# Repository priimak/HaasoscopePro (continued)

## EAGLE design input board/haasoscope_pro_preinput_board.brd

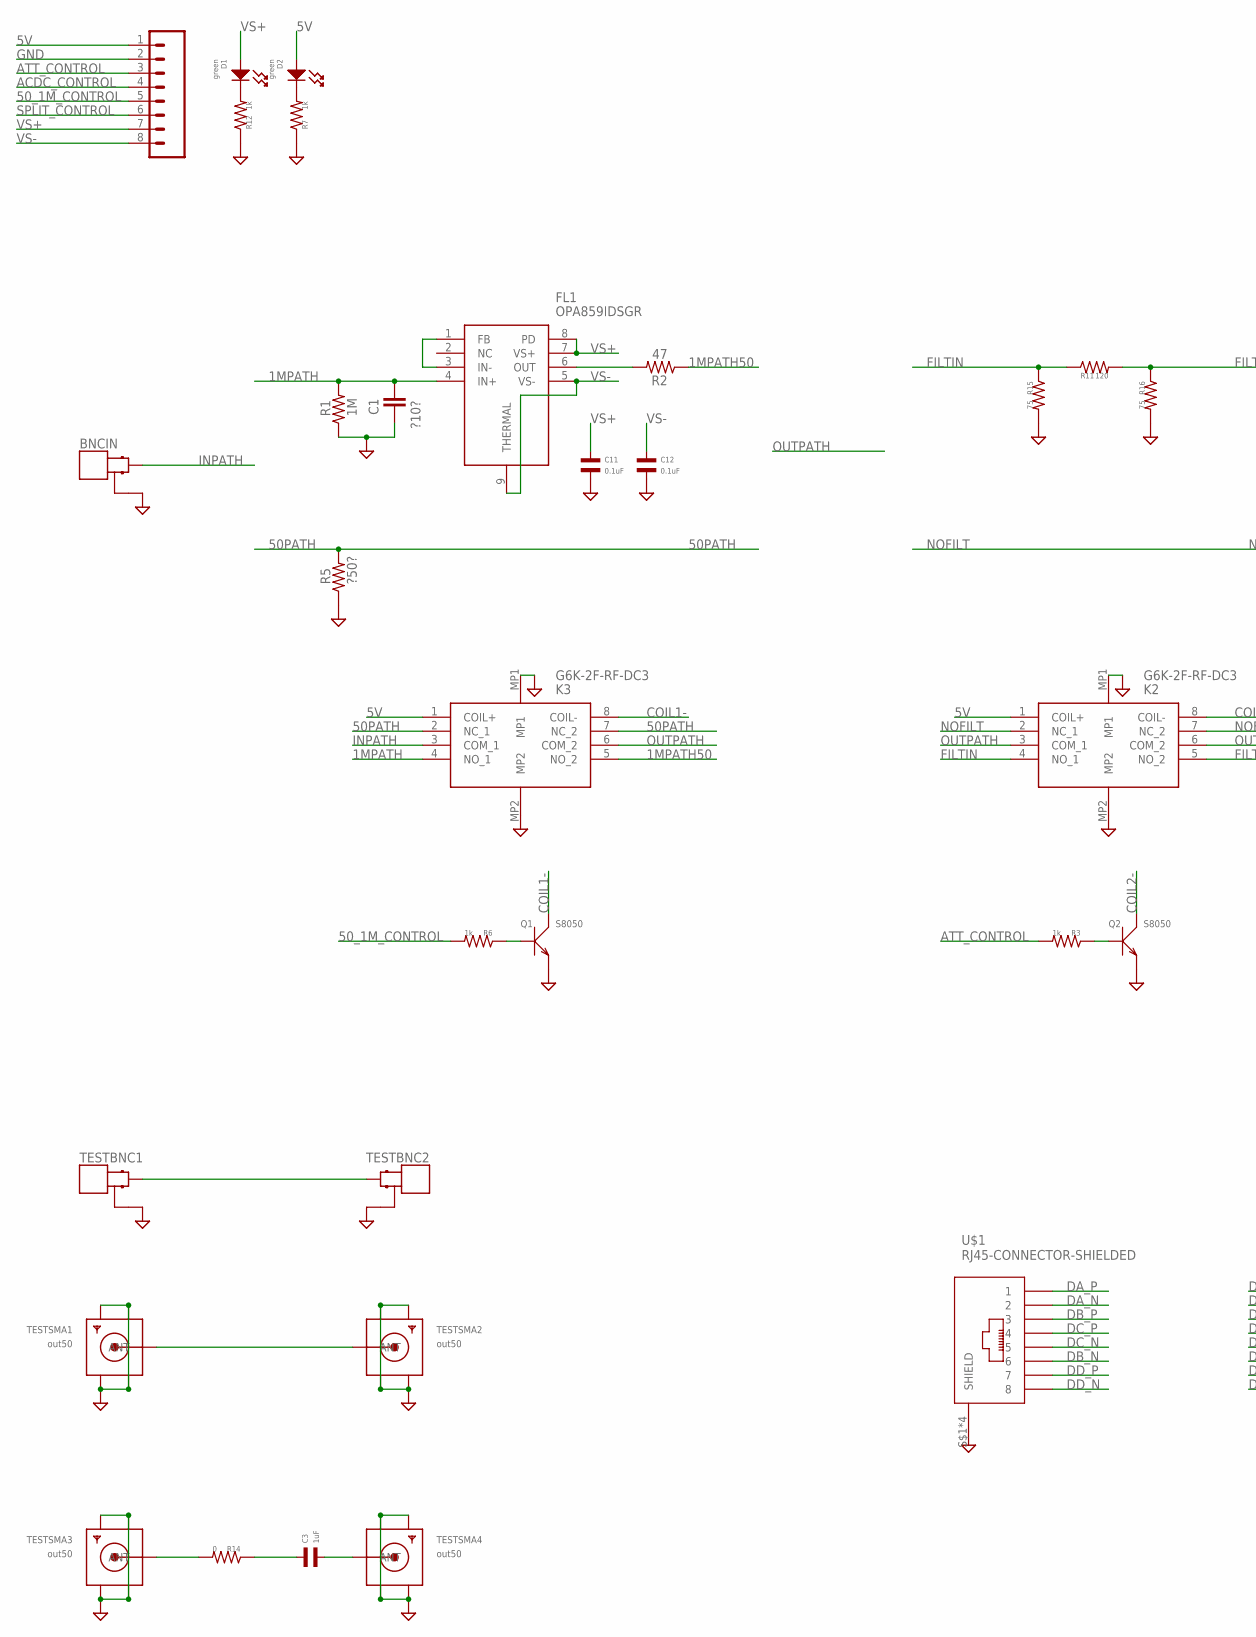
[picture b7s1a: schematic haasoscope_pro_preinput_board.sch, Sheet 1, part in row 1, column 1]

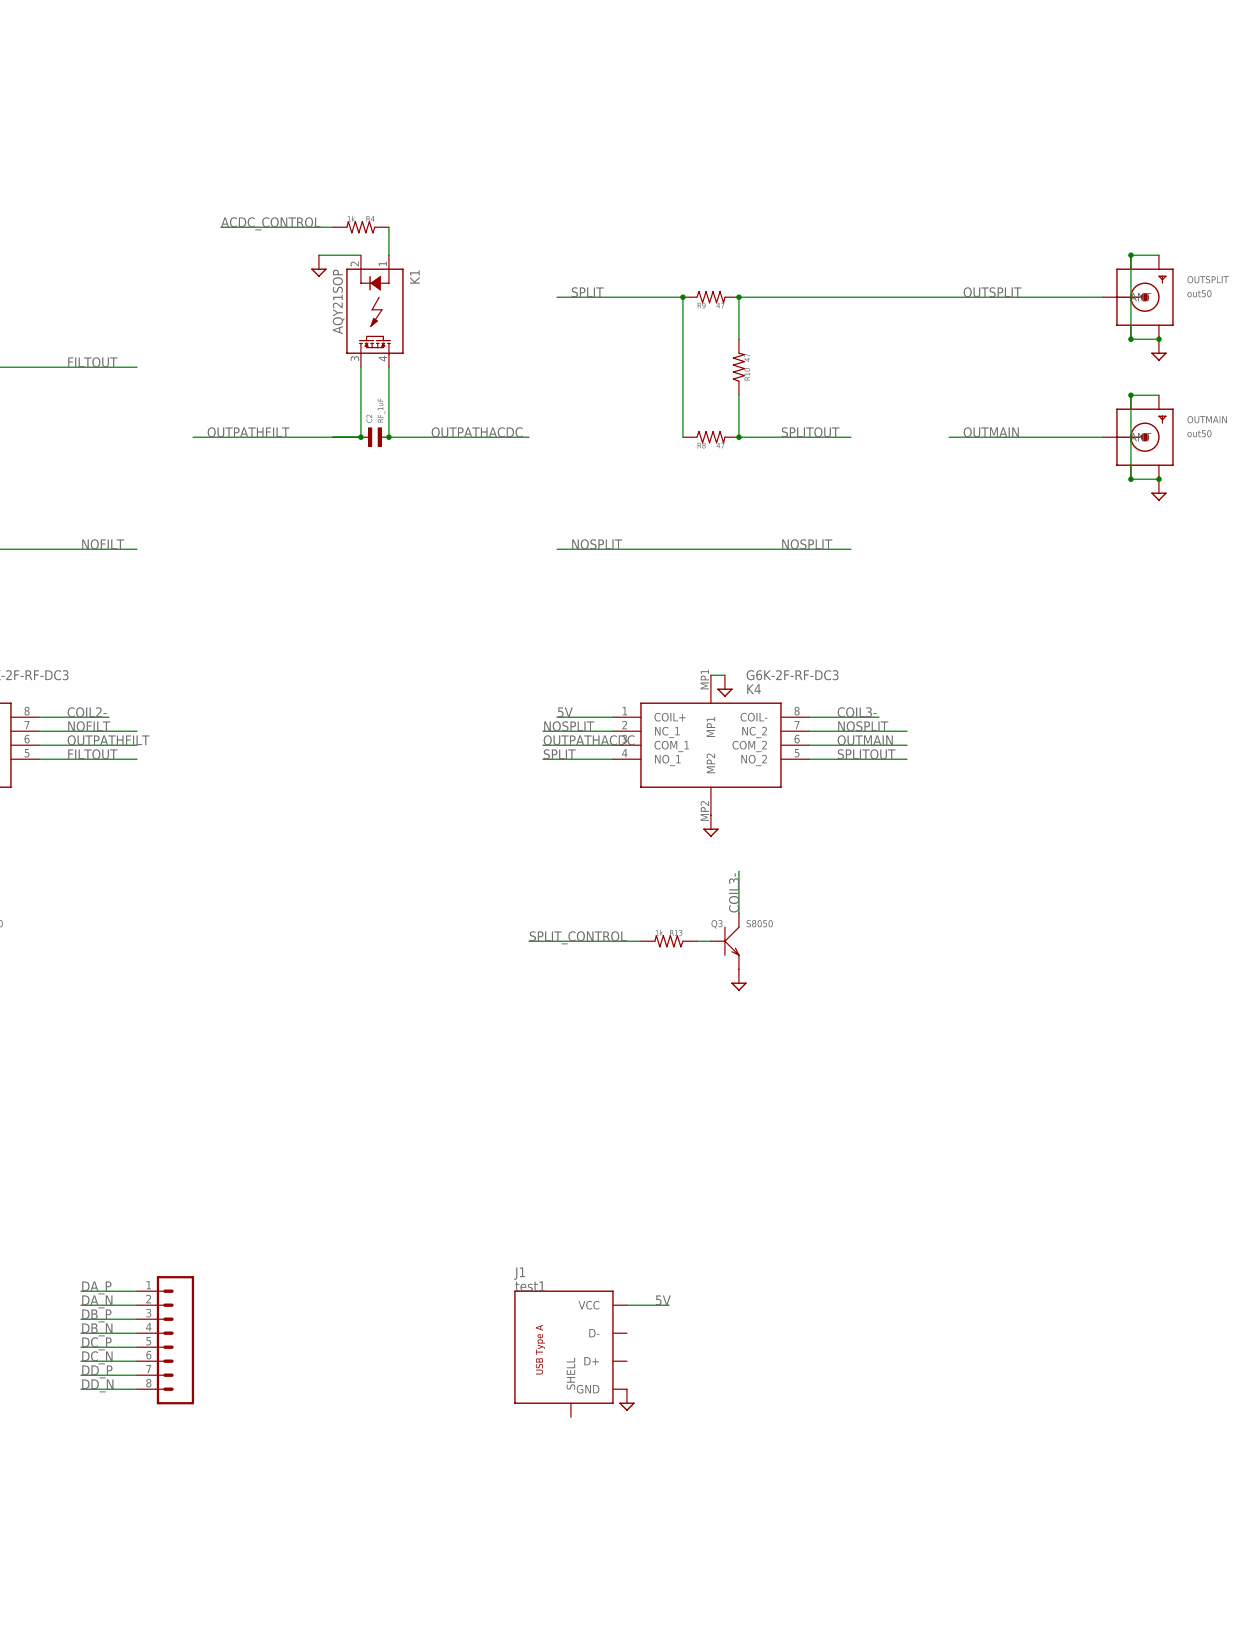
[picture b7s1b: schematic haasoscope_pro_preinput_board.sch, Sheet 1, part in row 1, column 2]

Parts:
BNCIN: MOLEX_BNC_73100-0105; MOLEX-BNC-73100-0105; MPN 73100-0105
C1: ?10?; C0805
C2: RF_1uF; C0402; LCSC C52923
C3: 1uF; C0402
C11, C12: 0.1uF; C0402
D1, D2: green; LED0603; LCSC C2286
FL1: OPA859IDSGR; SON50P200X200X80-9N
J1: test1; USB-2.0-A-THT-RA-TE_AMP-292303-1
J2, J4: 8pin; 1X08
K1: AQY21SOP; SOP04; MPN AQY210S; LCSC C7435105
K2, K3, K4: G6K-2F-RF-DC3; G6K2FRFDC3; LCSC C397195
OUTMAIN: out50; SMA_EDGELAUNCH
OUTSPLIT: out50; SMA_EDGELAUNCH
Q1, Q2, Q3: S8050; SOT-23; LCSC C7420370
R1: 1M; R0805
R2: 47; R0805
R3, R4, R6, R7, R12, R13: 1k; R0402
R5: ?50?; R0805
R8, R9, R10: 47; R0402
R11: 120; R0402
R14: 0; R0402
R15, R16: 75; R0402
TESTBNC1, TESTBNC2: MOLEX_BNC_73100-0105; MOLEX-BNC-73100-0105; MPN 73100-0105
TESTSMA1, TESTSMA2, TESTSMA3, TESTSMA4: out50; SMA_EDGELAUNCH
U$1: RJ45-CONNECTOR-SHIELDED; RJ45_THT_RA_AMPH-FRJAE448

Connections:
1MPATH: C1.2, FL1.4 (IN+), K3.4 (NO_1), R1.2
1MPATH50: K3.5 (NO_2), R2.1
5V: D2.ANODE, J1.P$1 (VCC), J4.1, K2.1 (COIL+), K3.1 (COIL+), K4.1 (COIL+)
50PATH: K3.2 (NC_1), K3.7 (NC_2), R5.2
50_1M_CONTROL: J4.5, R6.P$2
ACDC_CONTROL: J4.4, R4.P$2
ATT_CONTROL: J4.3, R3.P$2
COIL1-: K3.8 (COIL-), Q1.3 (C)
COIL2-: K2.8 (COIL-), Q2.3 (C)
COIL3-: K4.8 (COIL-), Q3.3 (C)
DA_N: J2.2, U$1.P$2 (2)
DA_P: J2.1, U$1.P$1 (1)
DB_N: J2.4, U$1.P$6 (6)
DB_P: J2.3, U$1.P$3 (3)
DC_N: J2.6, U$1.P$5 (5)
DC_P: J2.5, U$1.P$4 (4)
DD_N: J2.8, U$1.P$8 (8)
DD_P: J2.7, U$1.P$7 (7)
FILTIN: K2.4 (NO_1), R11.P$1, R15.P$1
FILTOUT: K2.5 (NO_2), R11.P$2, R16.P$1
GND: BNCIN.GND1 (GND), BNCIN.GND2 (GND), C1.1, C11.P$2, C12.P$2, J1.P$4 (GND), J4.2, K1.2 (K), K2.MP1, K2.MP2, K3.MP1, K3.MP2, K4.MP1, K4.MP2, OUTMAIN.GND@1 (GND4), OUTMAIN.GND@2 (GND3), OUTMAIN.GND@3 (GND2), OUTMAIN.GND@4 (GND1), OUTSPLIT.GND@1 (GND4), OUTSPLIT.GND@2 (GND3), OUTSPLIT.GND@3 (GND2), OUTSPLIT.GND@4 (GND1), Q1.2 (E), Q2.2 (E), Q3.2 (E), R1.1, R5.1, R7.P$1, R12.P$1, R15.P$2, R16.P$2, TESTBNC1.GND1 (GND), TESTBNC1.GND2 (GND), TESTBNC2.GND1 (GND), TESTBNC2.GND2 (GND), TESTSMA1.GND@1 (GND4), TESTSMA1.GND@2 (GND3), TESTSMA1.GND@3 (GND2), TESTSMA1.GND@4 (GND1), TESTSMA2.GND@1 (GND4), TESTSMA2.GND@2 (GND3), TESTSMA2.GND@3 (GND2), TESTSMA2.GND@4 (GND1), TESTSMA3.GND@1 (GND4), TESTSMA3.GND@2 (GND3), TESTSMA3.GND@3 (GND2), TESTSMA3.GND@4 (GND1), TESTSMA4.GND@1 (GND4), TESTSMA4.GND@2 (GND3), TESTSMA4.GND@3 (GND2), TESTSMA4.GND@4 (GND1), U$1.S$1 (SHIELD), U$1.S$2 (SHIELD), U$1.S$3 (SHIELD), U$1.S$4 (SHIELD)
INPATH: BNCIN.SIGNAL, K3.3 (COM_1)
unnamed: D1.CATHODE, R12.P$2
unnamed: Q2.1 (B), R3.P$1
unnamed: Q3.1 (B), R13.P$1
unnamed: FL1.6 (OUT), R2.2
unnamed: FL1.1 (FB), FL1.3 (IN-)
unnamed: Q1.1 (B), R6.P$1
unnamed: D2.CATHODE, R7.P$2
unnamed: TESTBNC1.SIGNAL, TESTBNC2.SIGNAL
unnamed: TESTSMA1.P (ANT), TESTSMA2.P (ANT)
unnamed: R14.P$2, TESTSMA3.P (ANT)
unnamed: K1.1 (A), R4.P$1
unnamed: C3.P$1, R14.P$1
unnamed: C3.P$2, TESTSMA4.P (ANT)
NOFILT: K2.2 (NC_1), K2.7 (NC_2)
NOSPLIT: K4.2 (NC_1), K4.7 (NC_2)
OUTMAIN: K4.6 (COM_2), OUTMAIN.P (ANT)
OUTPATH: K2.3 (COM_1), K3.6 (COM_2)
OUTPATHACDC: C2.P$2, K1.4 (DS1), K4.3 (COM_1)
OUTPATHFILT: C2.P$1, K1.3 (DS2), K2.6 (COM_2)
OUTSPLIT: OUTSPLIT.P (ANT), R9.P$2, R10.P$2
SPLIT: K4.4 (NO_1), R8.P$1, R9.P$1
SPLITOUT: K4.5 (NO_2), R8.P$2, R10.P$1
SPLIT_CONTROL: J4.6, R13.P$2
VS+: C11.P$1, D1.ANODE, FL1.7 (VS+), FL1.8 (PD), J4.7
VS-: C12.P$1, FL1.5 (VS-), FL1.9 (THERMAL), J4.8

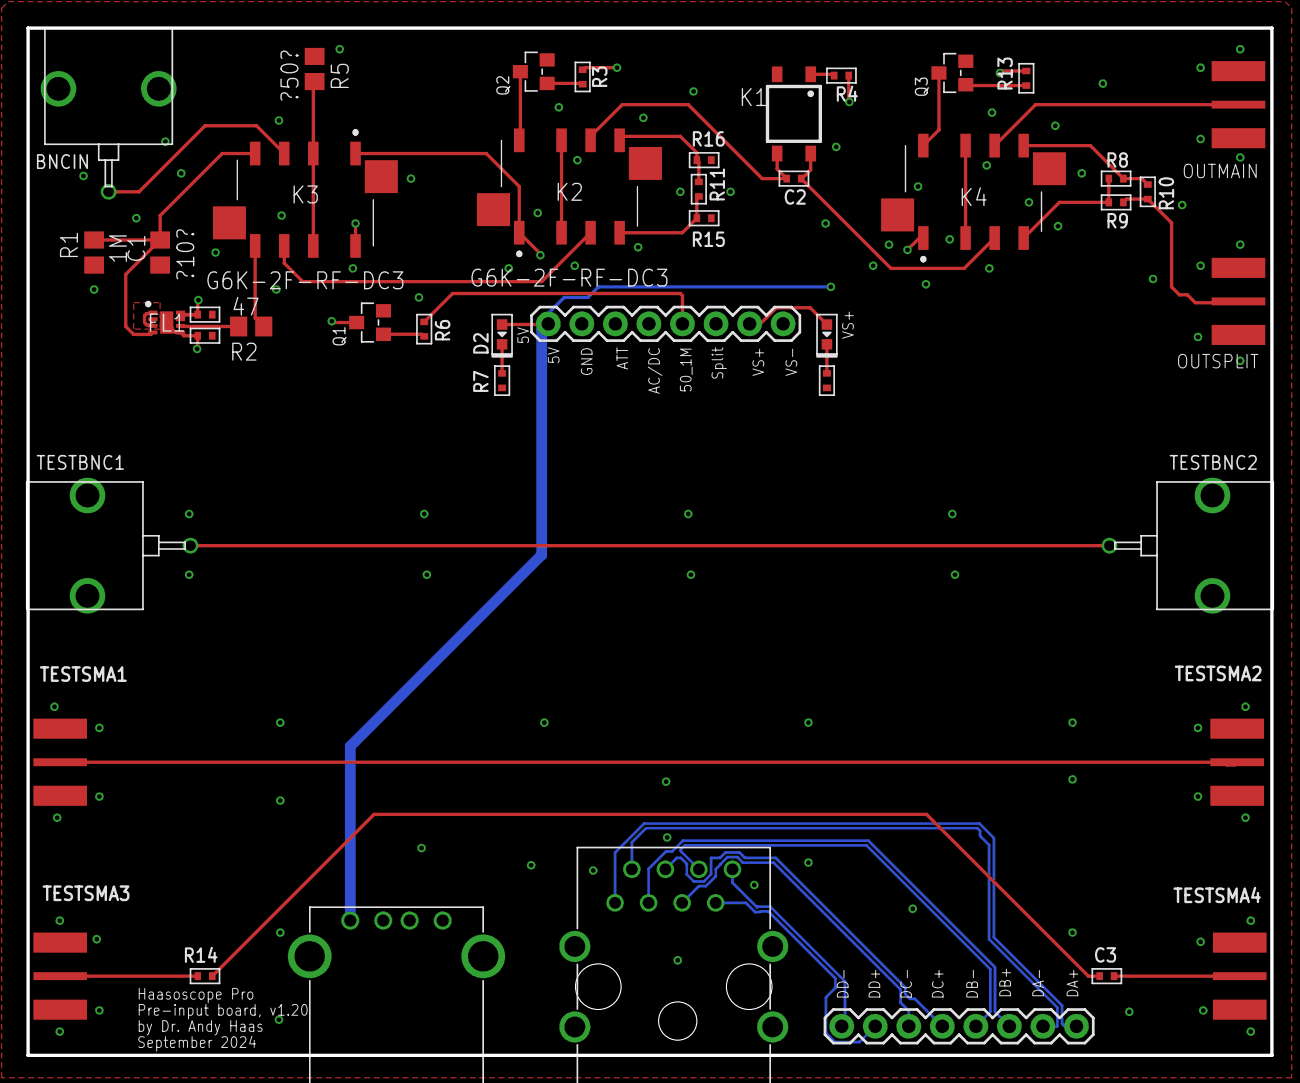
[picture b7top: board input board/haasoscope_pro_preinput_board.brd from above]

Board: 4 copper layers, 94.2 x 77.8 mm, 44 parts (0 on the bottom side), 47 nets.

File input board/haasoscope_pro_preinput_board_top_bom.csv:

Comment,Designator,Footprint,LCSC Part #
0.1uF,C11 C12,C0402,
1M,R1,R0805,
1k,R4 R6 R7 R12,R0402,
1uF,C2,C0805,
10pF,C1,C0805,
47,R2 R8 R9 R10,R0805,
75,R13 R14,R0805,
120,R11,R0805,
?50?,R5,R0805,
AQY21SOP,K1,SOP04,C7435105
G6K-2F-RF-DC3,K3,G6K2FRFDC3,
OPA859IDSGR,FL1,SON50P200X200X80-9N,
S8050,Q1,SOT-23,C7420370
green,D1 D2,LED0603,
in,INCON,SMA_EDGELAUNCH,
out50,OUTPUT501 OUTPUT502,SMA_EDGELAUNCH,

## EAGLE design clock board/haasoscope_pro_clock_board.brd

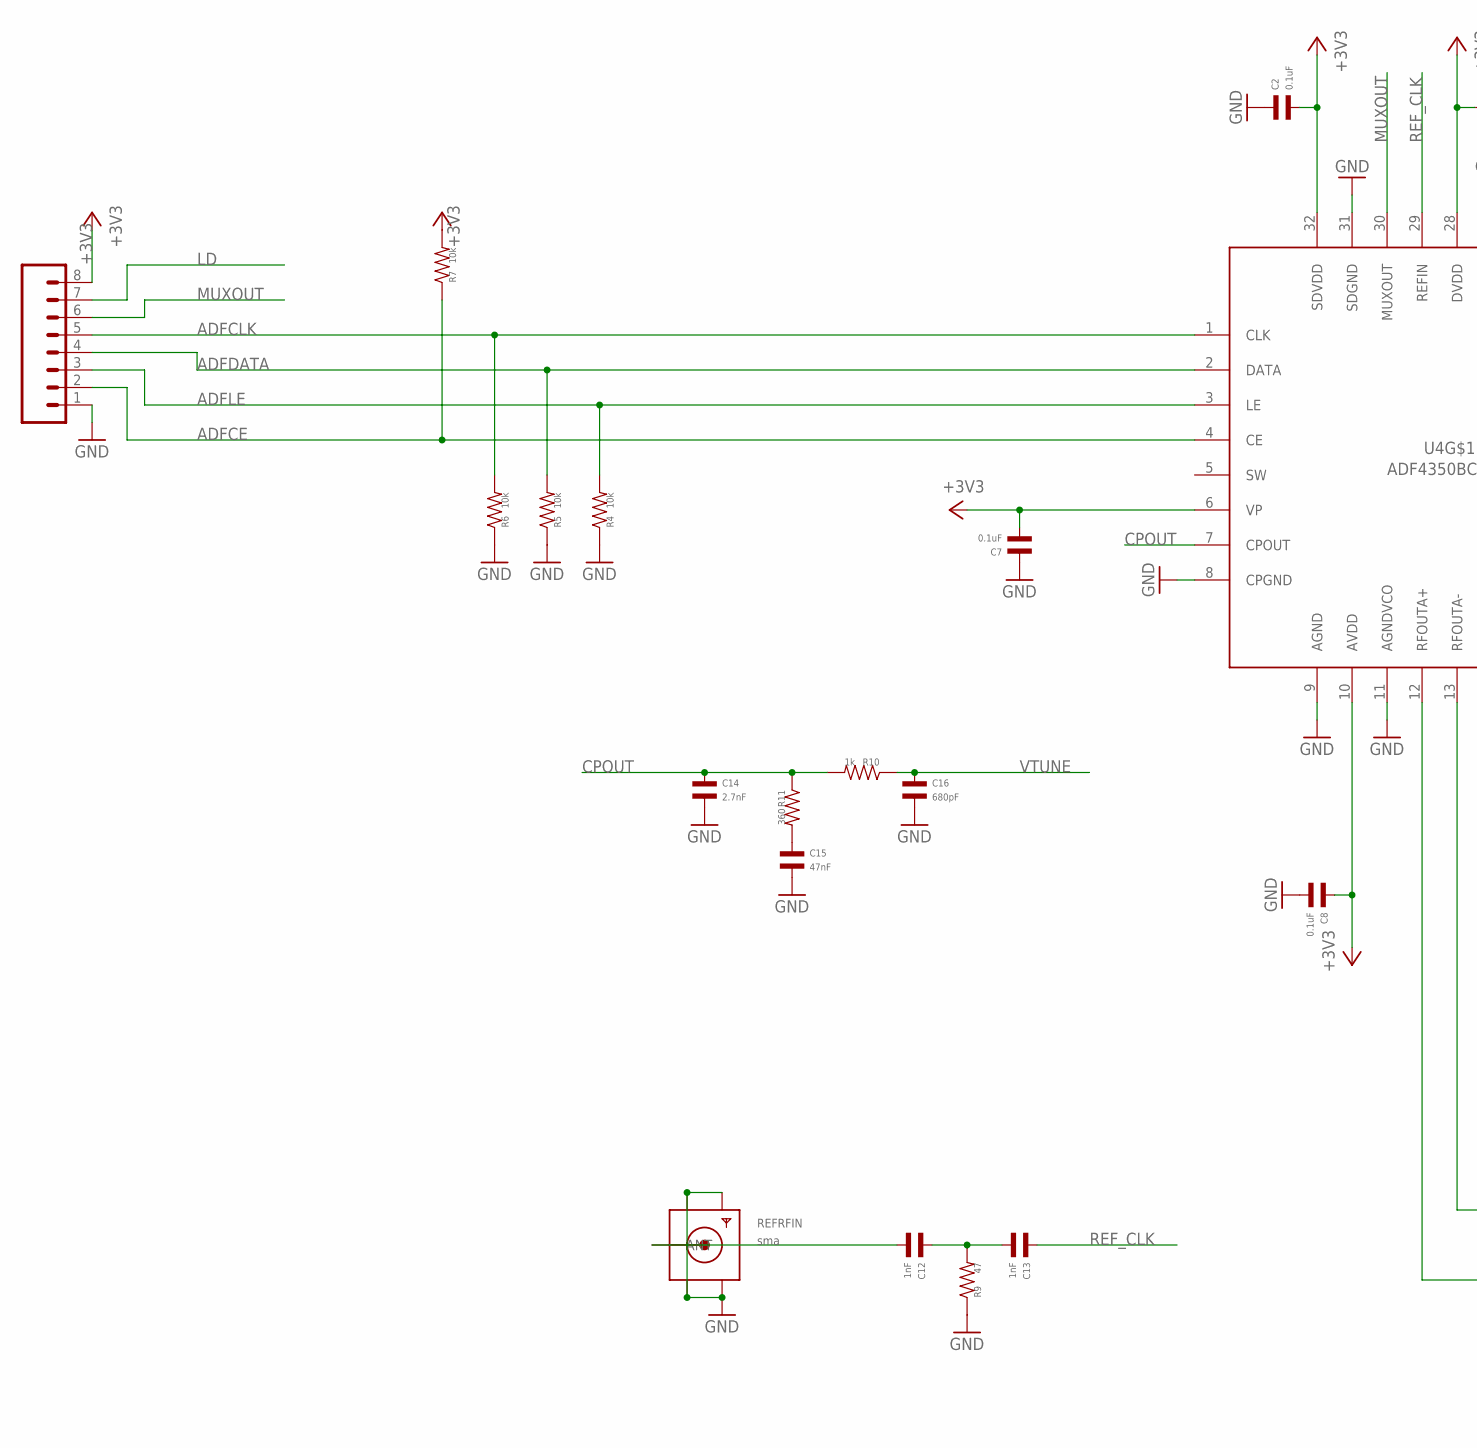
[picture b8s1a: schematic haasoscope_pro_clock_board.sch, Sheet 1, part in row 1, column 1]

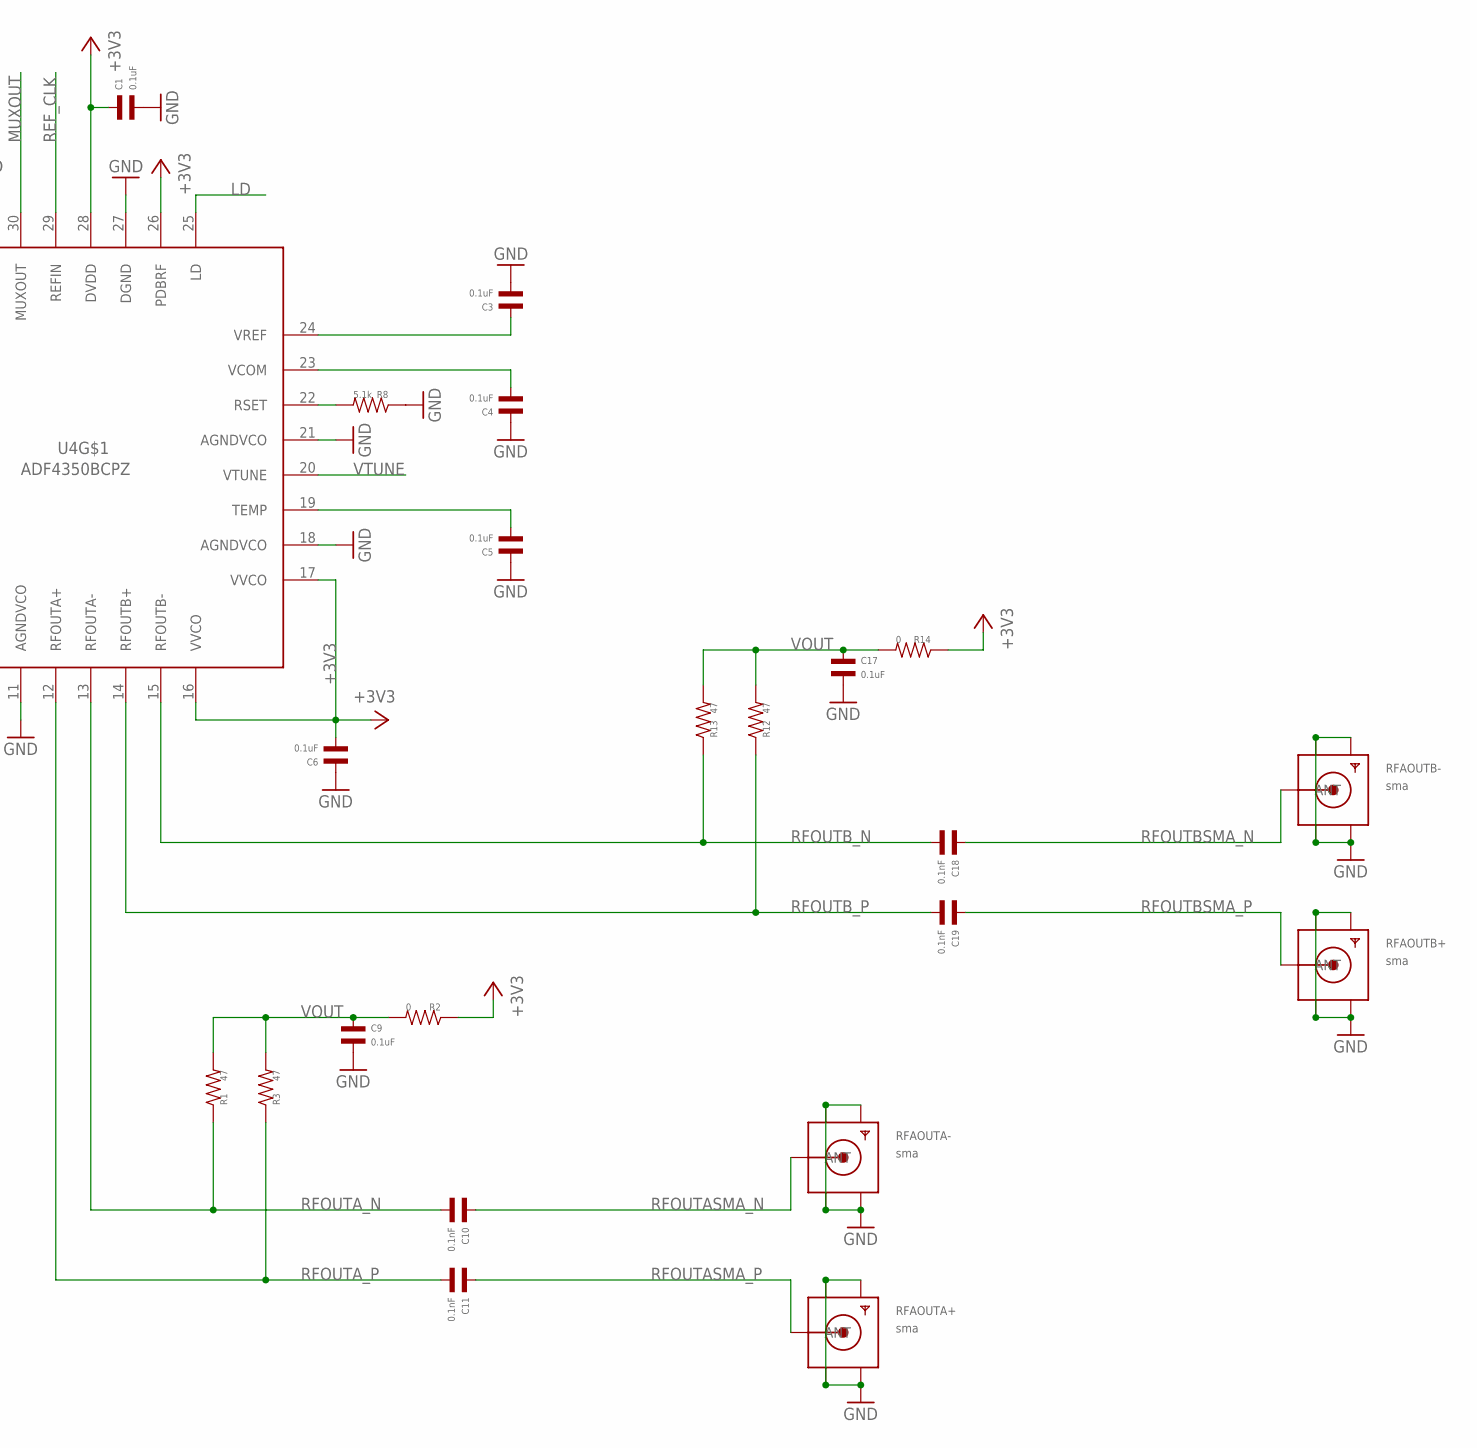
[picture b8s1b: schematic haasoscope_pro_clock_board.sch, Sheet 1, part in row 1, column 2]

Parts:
C1, C2, C3, C4, C5, C6, C7, C8, C9, C17: 0.1uF; C0402
C10, C11, C18, C19: 0.1nF; C0402
C12, C13: 1nF; C0402
C14: 2.7nF; C0402
C15: 47nF; C0402
C16: 680pF; C0402
J4: 8pin; 1X08
R1, R3, R9, R12, R13: 47; R0402
R2, R14: 0; R0402
R4, R5, R6, R7: 10k; R0402
R8: 5.1k; R0402
R10: 1k; R0402
R11: 360; R0402
REFRFIN: sma; SMA_EDGELAUNCH
RFAOUTA+: sma; SMA_EDGELAUNCH
RFAOUTA-: sma; SMA_EDGELAUNCH
RFAOUTB+: sma; SMA_EDGELAUNCH
RFAOUTB-: sma; SMA_EDGELAUNCH
U4: ADF4350BCPZ; QFN50P500X500X100-33V2N

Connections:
+3V3: C1.P$1, C2.P$2, C6.P$2, C7.P$2, C8.P$1, J4.8, R2.P$1, R7.P$2, R14.P$1, U4.6 (VP), U4.10 (AVDD), U4.16 (VVCO), U4.17 (VVCO), U4.26 (PDBRF), U4.28 (DVDD), U4.32 (SDVDD)
ADFCE: J4.2, R7.P$1, U4.4 (CE)
ADFCLK: J4.5, R6.P$2, U4.1 (CLK)
ADFDATA: J4.4, R5.P$2, U4.2 (DATA)
ADFLE: J4.3, R4.P$2, U4.3 (LE)
CPOUT: C14.P$1, R10.P$2, R11.P$1, U4.7 (CPOUT)
GND: C1.P$2, C2.P$1, C3.P$2, C4.P$1, C5.P$1, C6.P$1, C7.P$1, C8.P$2, C9.P$2, C14.P$2, C15.P$2, C16.P$2, C17.P$2, J4.1, R4.P$1, R5.P$1, R6.P$1, R8.P$1, R9.P$1, REFRFIN.GND@1 (GND4), REFRFIN.GND@2 (GND3), REFRFIN.GND@3 (GND2), REFRFIN.GND@4 (GND1), RFAOUTA+.GND@1 (GND4), RFAOUTA+.GND@2 (GND3), RFAOUTA+.GND@3 (GND2), RFAOUTA+.GND@4 (GND1), RFAOUTA-.GND@1 (GND4), RFAOUTA-.GND@2 (GND3), RFAOUTA-.GND@3 (GND2), RFAOUTA-.GND@4 (GND1), RFAOUTB+.GND@1 (GND4), RFAOUTB+.GND@2 (GND3), RFAOUTB+.GND@3 (GND2), RFAOUTB+.GND@4 (GND1), RFAOUTB-.GND@1 (GND4), RFAOUTB-.GND@2 (GND3), RFAOUTB-.GND@3 (GND2), RFAOUTB-.GND@4 (GND1), U4.8 (CPGND), U4.9 (AGND), U4.11 (AGNDVCO), U4.18 (AGNDVCO), U4.21 (AGNDVCO), U4.27 (DGND), U4.31 (SDGND), U4.PAD@1_1 (GND), U4.PAD@1_2 (GND), U4.PAD@1_3 (GND), U4.PAD@2_1 (GND), U4.PAD@2_2 (GND), U4.PAD@2_3 (GND), U4.PAD@3_1 (GND), U4.PAD@3_2 (GND), U4.PAD@3_3 (GND)
LD: J4.7, U4.25 (LD)
MUXOUT: J4.6, U4.30 (MUXOUT)
unnamed: C12.P$2, REFRFIN.P (ANT)
unnamed: C12.P$1, C13.P$2, R9.P$2
unnamed: C15.P$1, R11.P$2
unnamed: C5.P$2, U4.19 (TEMP)
unnamed: C4.P$2, U4.23 (VCOM)
unnamed: R8.P$2, U4.22 (RSET)
REF_CLK: C13.P$1, U4.29 (REFIN)
RFOUTASMA_N: C10.P$1, RFAOUTA-.P (ANT)
RFOUTASMA_P: C11.P$1, RFAOUTA+.P (ANT)
RFOUTA_N: C10.P$2, R1.P$1, U4.13 (RFOUTA-)
RFOUTA_P: C11.P$2, R3.P$1, U4.12 (RFOUTA+)
RFOUTBSMA_N: C18.P$1, RFAOUTB-.P (ANT)
RFOUTBSMA_P: C19.P$1, RFAOUTB+.P (ANT)
RFOUTB_N: C18.P$2, R13.P$1, U4.15 (RFOUTB-)
RFOUTB_P: C19.P$2, R12.P$1, U4.14 (RFOUTB+)
VOUT: C9.P$1, C17.P$1, R1.P$2, R2.P$2, R3.P$2, R12.P$2, R13.P$2, R14.P$2
VREF: C3.P$1, U4.24 (VREF)
VTUNE: C16.P$1, R10.P$1, U4.20 (VTUNE)

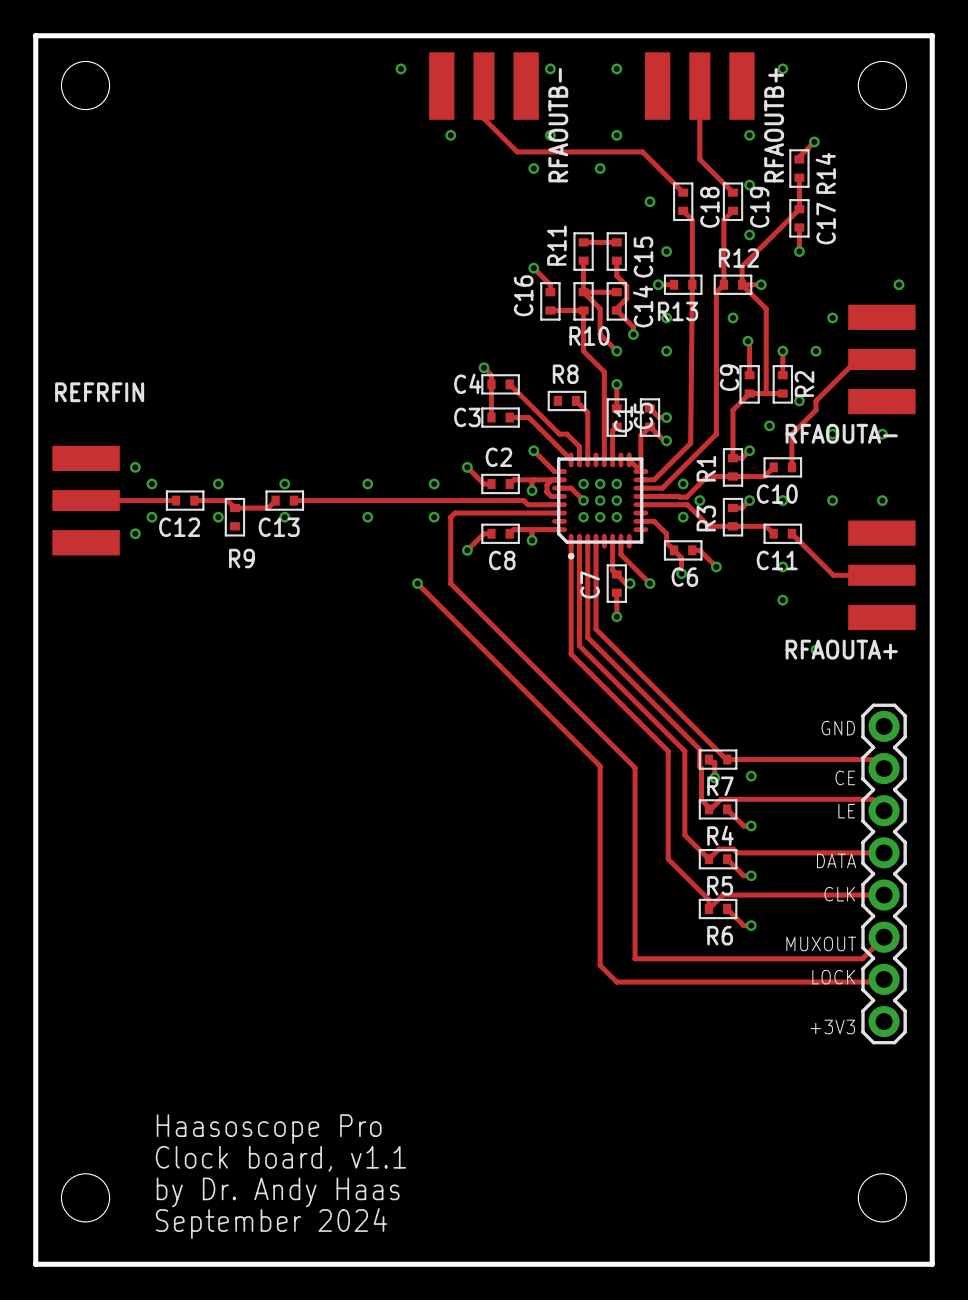
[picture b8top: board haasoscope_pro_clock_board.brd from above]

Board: 4 copper layers, 54.0 x 74.0 mm, 40 parts (0 on the bottom side), 27 nets.

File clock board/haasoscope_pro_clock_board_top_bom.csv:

Comment,Designator,Footprint,LCSC Part #
0,REFRFIN RFAOUT+ RFAOUT- R2,R0402,
0.1nF,C10 C11,C0402,
0.1uF,C1 C2 C3 C4 C5 C6 C7 C8 C9,C0402,
1k,R10,R0402,
1nF,C12 C13,C0402,
2.7nF,C14,C0402,
5.1k,R8,R0402,
10k,R4 R5 R6 R7,R0402,
47,R1 R3 R9,R0402,
47nF,C15,C0402,
360,R11,R0402,
680pF,C16,C0402,
ADF4350BCPZ,U4,QFN50P500X500X100-33V2N,

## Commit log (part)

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2024-10-03 remap lvds in/out clk, spare01, trig start to route them
2024-10-03 more routing
2024-10-04 reduce BOM
2024-10-04 specify part for LMR33630ADDA
2024-10-04 ready to do gnd vias, then routing rest
2024-10-04 moved some things around etc
2024-10-04 gnds etc
2024-10-05 ready to route rest?
2024-10-05 fixed some bad route paths
2024-10-05 minor, add sch pdf
2024-10-05 move lvdsin resistors to BOTTOM of board
2024-10-06 did some cutouts
2024-10-06 minor vias etc
2024-10-06 add more connectors
2024-10-07 move connectors a little
2024-10-07 adjust connectors a little
2024-10-07 move everything down by 3.5mm (one board slot) to make room for eth connectors
2024-10-07 add 10kHz output for probe comp
2024-10-08 Use dual-port RAM buffer instead of FIFO
2024-10-09 Add trigger point
2024-10-09 Add trigger pos
2024-10-09 Timing closure
2024-10-09 fix compliler warnings, better min/max
2024-10-09 add rising trigger
2024-10-10 ad trigger lines
2024-10-10 add fan connector and control
2024-10-11 add ToT to trigger
2024-10-11 make thresholdDelta a spinbox instead of a slider
2024-10-11 add adiff netclass, 4 mil wide with 5 mil spacing
2024-10-11 Move fan connector a bit away from USB lines
2024-10-11 Fix warnings
2024-10-11 can do downsample
2024-10-11 highres working, but averaging over samples, not within 40 samples
2024-10-12 downsample merging of 40 samples
2024-10-12 downsample merging of 2,4,8,20 samples too
2024-10-12 closed timing, using agressive setting
2024-10-12 always use the same clk and str bits during downsampling
2024-10-12 show stats in status bar instead of plot title
2024-10-12 show stats less often, and while not drawing
2024-10-12 fix bug with xaxis scaling at big downsample
2024-10-13 fix diffpair net classes and usb_c diffpair impedance
2024-10-13 fix isolation of gnd pours from 0 (.09mm) to .1524mm, now traces are 50 ohm at .254mm width, but before they were more like 44 ohm
2024-10-13 Typo
2024-10-15 Rise time better, using fit
2024-10-15 Controls for 50/1M, Att, ACDC, Oversamp
2024-10-17 move fan so it doesn't hit relay
2024-10-17 change cs=2 to cs=3 for clk, for v1.0 board, add att check
2024-10-17 adjustable fitwidth, adjust phases for v1.00
2024-10-17 remove static
2024-10-17 risetime better
2024-10-18 set clkout current to 4mA
2024-10-18 tad adjust
2024-10-18 simplify clocks
2024-10-18 dacoffset for chan A
2024-10-18 put back clk cap
2024-10-18 v23.1
2024-10-18 make 4.5mm longer
2024-10-21 remove "50ohm?" pads (causing BW drop at 2 GHz)
2024-10-22 add -T relay, and new ACDC SSR
2024-10-22 use new T relays, re-layout
2024-10-23 make 2v5+ from 3v3 instead of 2v8+, make 1v2 from 1v5d using standard TPS7A7200RGTR instead of 3v3 with ams117-1.2
2024-10-23 finish routing
2024-10-23 fix hole positions
2024-10-23 change -2v8 to -3v0 for more dropout headroom on -2v5 regulator
2024-10-24 minor
2024-10-24 try no thermals, cutouts under relays
2024-10-24 tests
2024-10-24 rename photoMOS to 3475R
2024-10-24 test clkswitch, lvds, printing slowdac voltages
2024-10-24 probe compensation output
2024-10-25 probe compensation output at 1kHz
2024-10-27 2 channels, sort of
2024-10-28 2 channels, mostly working, no downsampling downsampling working for 1 channel
2024-10-28 invert correct channels, fix triggers adjust according to sample triggered
2024-10-28 downsampling working for two channels for dsm=2
2024-10-29 minor trig fix
2024-10-29 correct for triggered sample when downsampling?
2024-10-29 be careful when inverting samples
2024-10-29 minor fix to downsampling
2024-10-29 Open list of USBs
2024-10-29 Use multiple usb devices
2024-10-31 Move 12V and JTAG connectors back slightly, by 1 and 3mm respectively
2024-10-31 working on trigger jitter
2024-10-31 use cutouts under relays
2024-10-31 use cutouts under 3GHz relays
2024-10-31 move clk_ext a little
2024-10-31 working probe comp
2024-10-31 set voltage scale etc
2024-11-01 consistent 1 and 2 channel behavior
2024-11-01 ext trig
2024-11-02 ext trig synced
2024-11-02 colors
2024-11-03 use 0.35mm vias instead of a few 0.5mm ones
2024-11-04 sample_triggered working, for downsampling 1, single channel
2024-11-05 sample_triggered working, for all downsampling
2024-11-05 sample_triggered working, for two boards, not workng for downsampling yet on two boards
2024-11-05 sample_triggered working, for two boards, including downsampling, and two channels per board
2024-11-05 color indicator for active channel and board
2024-11-05 better clk switching
2024-11-07 import adf435x_core instead of extra library
2024-11-07 for mac
2024-11-07 Revert "for mac"
    This reverts commit f7b2680cb1f74eca6fe820a2ef46b72208b7e202.
2024-11-07 qtgui
2024-11-08 pyinstaller windows
2024-11-08 pyinstaller mac
2024-11-08 pyinstaller zips ignore
2024-11-08 acdc and normal/auto fixes
2024-11-08 linux driver
2024-11-09 either board 1 or 0 can be the exttrig one
2024-11-09 cleanup, find first usb
2024-11-10 triggerpos and risetime per channel
2024-11-10 calculate std between oversampled channels, add egain to adjust gain between them
2024-11-10 calculate average std between oversampled channels
2024-11-11 Add 1kHzOut50 SMA and ExtTrigIn SMA on back panel
2024-11-11 Aux out
2024-11-11 Add GND planes
2024-11-12 Add a resistor on the 50 ohm aux out line
2024-11-12 1kHz
2024-11-12 cleanup schematics
2024-11-14 markdown
2024-11-14 only calculate std between boards when there's more than 1 board
2024-11-17 fix a mac glitch
2024-11-18 detect 12V and disconnect 5V from USB
2024-11-18 Add comparitors of CC1/2 to 0.7V for USB C power detection
2024-11-18 reprint
2024-11-19 LVDS trig backwards H2/H1 outspare1 now intrigb F21/F22 inspare1 now outtrigb
2024-11-21 remove old stuff
2024-11-21 move test boards to sub boards directory
2024-11-21 README: power instructions Board: Fan marking
2024-11-22 move ftdi template
2024-11-22 fix bug in usb reordering, add back mounting holes
2024-11-23 selected channel fix
2024-11-24 for startup on mac
2024-11-24 Deemphasis filter
2024-11-25 27 pF
2024-11-25 logo
2024-11-26 cutout gnd on top layer below sma other minor aesthetic changes
2024-11-26 switch to TLP3475 from TLP3475, because of availability
2024-11-30 Update README.md with hackaday io
2024-12-07 3475R -> 3475 in sch and brd
2024-12-07 a bit neater
2024-12-09 working on fpga symbol
2024-12-09 adc symbol
2024-12-09 adc symbol done
2024-12-09 minor sch updates
2024-12-10 minor sch updates, discovered during KiCAD import
2024-12-10 fit extrig data to other channel RMS and mean fix sample_triggered for slower risetime events quiet TAD message tot can go down to 0 more lvdsout_trig=0
2024-12-12 fixes for sample_triggered only working perfect for tot=0
2024-12-13 add 27 Ohm + 27 pF parallel path to outsplit
2024-12-18 357 -> 220 Ohm for lmh5401 termination 27 -> 16 pF and 27 -> 47 Ohm for splitter
2024-12-18 restructure
2024-12-18 reorder startup so calib issue is gone
2024-12-18 get usb board setups right after power up
2024-12-19 cap labels
2024-12-20 update and reroute debugout boardin boardout
2024-12-22 update filter component values
2024-12-24 added filter test
2024-12-24 update filter values, 5th order
2024-12-24 calibrate risetime
2024-12-24 added input 0 filters
2024-12-25 move eval board files
2024-12-25 fix parts
2024-12-25 Use smaller 0201 resistor footprint Board v1.23 does not include this change or any future changes
2024-12-28 v1.24
2024-12-28 v1.24, rotations in cpl
2024-12-28 out50 -> 50 in BOM
2024-12-28 add rgb leds
2024-12-29 move text
2024-12-29 gnd on top too
2024-12-29 remove old gerbers
2024-12-29 move led2 and led3, use led3 for front panel LEDs
2024-12-29 fix sync slot bug
2024-12-29 add neopixel LED control
2024-12-30 add pin1 indicator for Y3
2024-12-30 Revert "add smt images"
    This reverts commit 91127cac69ce54283d65aa94f665c132e5e7b86a.
2025-01-01 add BOM
2025-01-02 add FFT plot
2025-01-03 set LEDs for front panel
2025-01-04 cleaned up schematics a little
2025-01-04 add much more filtering of 5V input
2025-01-04 use 1000 uF caps
2025-01-04 inductor rotations
2025-01-05 specify part for 93LC56B
2025-01-05 more ports on scematic and other cosmetic changes
2025-01-05 added frames, updated FPGA symbol so it fits in frame
2025-01-06 added more xref
2025-01-06 put 1000 uF caps on buck outputs
2025-01-07 minor routing
2025-01-08 add 10uF Cin caps, and move them and the 0.1uF close to PGND for switching regs, hoping to reduce EMI
2025-01-08 cut off unshifted data on right
2025-01-08 adjust V scale
2025-01-12 switch between one and two channels dynamically - likely still many little bugs, needs testing
2025-01-13 reverse D and S on P-mos, and divide down 12connected to 2.5V for FPGA input so it's not pulled down to 3V
2025-01-14 update cap values for filters
2025-01-14 dimmer leds
2025-01-16 add light pipes for front leds
2025-01-16 add leds on main board under light pipes
2025-01-16 add light pipe holes and remove leds
2025-01-17 add 1kHzout and gnd tabs and cutouts on front panel
2025-01-19 fix minor timing warning
2025-01-19 do averaging for downsample > 5 make sure to pre-aquire enough samples
2025-01-19 adjust number of presamples to take before trigger, based on triggerpos
2025-01-21 adjust ram_address_triggered for tot
2025-01-22 add pipeline for no downsampling too so timing is consistent
2025-01-22 extra downsampling also in two channel mode
2025-01-23 use signed addition for all highres fix bug in triggercounter use triggersamplecounter to see how long to wait to for tot
2025-01-23 trigger vline
2025-01-23 fix downsamplemerging_triggered for tot>0
2025-01-23 dorolling, auto/normal trigger better initial clock phase detection / adjustment
2025-01-23 downsamplezoom clean up some printouts
2025-01-24 offset scaling
2025-01-24 scaling and tenx
2025-01-24 cleanup led code
2025-01-30 make input 0 on the left, but switch to input 1 for oversampling
2025-01-30 move leds slightly, rotate tabs
2025-01-30 better settings for two boards and oversampling
2025-01-31 dointerleaved fft
2025-01-31 adjust toff for downsamplefactor
2025-01-31 fix downsamplemergingcounter_triggered for tot>0 and ext_trig
2025-01-31 do autocalib for toff
2025-01-31 dynamic mem depth
2025-01-31 minor speed up
2025-01-31 account for oversampling in setup and in acdc
2025-01-31 v1.26
2025-02-03 add smas
2025-02-03 get rid of triggersamplecounter slightly better auto trigger
2025-02-03 move offsets better
2025-02-03 fix rolling and ext trig
2025-02-03 add clk_ext to bdf file and sdc for easy switching clean up and label bdf
2025-02-03 calc mean and std correction for oversampling in autocalib function
2025-02-03 fix offset values
2025-02-03 adjust offset and gain for oversampling
2025-02-04 add upsampling
2025-02-04 adjust gain for other oversampled channel better
2025-02-04 show all pins on .bdf
2025-02-05 minor, gnd vias under usbs 5v ports, to connect bottom gnd pour
2025-02-05 minor, keep fft variables in fftui class
2025-02-05 move pads a little (~2 mil) closer for MF_PASSIVES R and C 0402 package, to fix JLCPCB complaint
2025-02-05 allow for negative TAD, which flips clk polarity
2025-02-08 fit schematic on page
2025-02-08 remove test filter
2025-02-10 minor cosmetics
2025-02-10 update fcc marking
2025-02-11 include safety files
2025-02-21 add DoC for cable
2025-02-23 1k for 12VConnected
2025-02-23 LED colors
2025-02-23 use vias, so gnd is connected to screws (?)
2025-02-24 rename
2025-02-25 add caps for LEDs
2025-02-27 adjust offset scale
2025-02-27 edit power tips add info on editing GUI
2025-03-10 Update README.md with link to usb blaster hints
2025-03-11 Update README.md with pointer to firmware readme
2025-03-12 Update README.md with screenshots
2025-03-14 Clean up
2025-03-14 compiled after Dmitri cleanup
2025-03-15 If statement reversal to reduce LUT usage.
    Reduces total logic elements used from 13568 to 13454.
2025-03-15 A bit more minor formatting improvements
2025-03-15 compiled after Dmitri cleanup again, and put babk 8'd1 s
2025-03-17 Minor readbility improvement
2025-03-19 Super minor clean up and indent change
2025-03-20 A better pllphase detection, make sure we take events with new phase before adjusting
2025-03-20 A better pllphase detection, up 5 for test, then down 2 Pull out those parameters
2025-03-21 udev for linux
2025-03-21 Update README.md with Linux tips
2025-03-21 Update README.md with instructions for Linux etc
2025-03-21 Latest jic
